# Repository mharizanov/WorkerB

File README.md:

WorkerB
=======

This is my latest project, the “Worker Bee”. It is an ATMega32U4-based Arduino compatible board running at 8Mhz, 
specially designed for low-power battery operation. There is a slot on the board to fit a 2.4Ghz nRF24L01 breakout 
module (not included, optional); Power to that slot is controlled via a MOSFET, so that the MCU is in control and 
can power the nRF24L01 whenever/if necessary and save power.

The board can be powered via a single AAA battery using an optional LTC3525 boost regulator, a CR2032 battery or 
any other 2.6-5.5V source (via the on-board MCP1700 for voltages >3.3V or directly at the VCC in)

http://harizanov.com/product/workerb/

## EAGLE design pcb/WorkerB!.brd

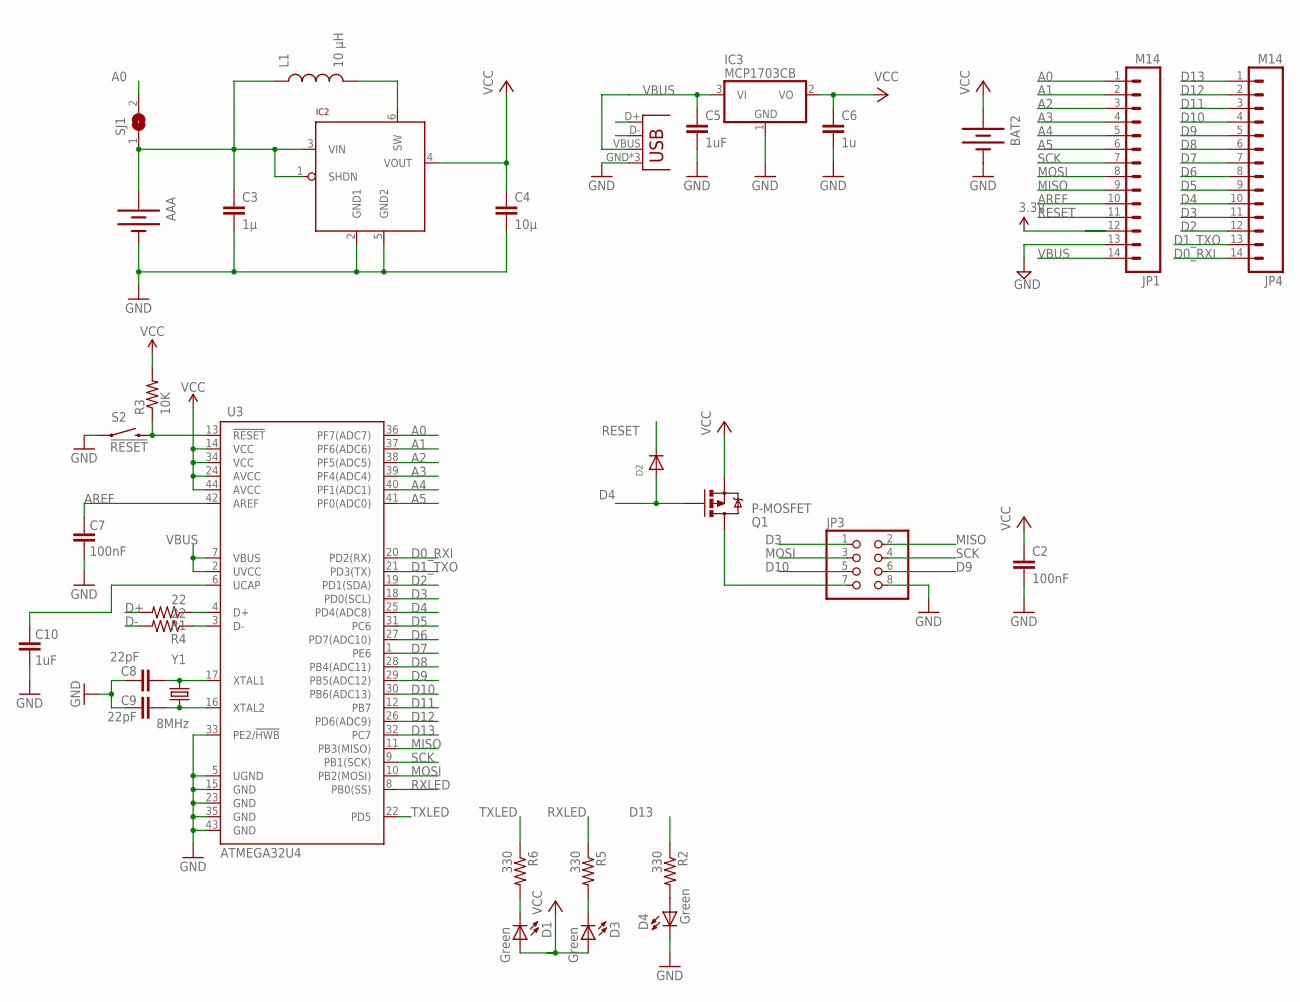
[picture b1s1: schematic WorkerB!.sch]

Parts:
AAA: BATTERYAAA-JL; BATTERY-AAA-JL
BAT2: BATTERY20PTH; BATTCOM_20MM_PTH
C2: 100nF; C0603K
C3: 1µ; 0603-CAP
C4: 10µ; 0805
C5: 1uF; C0603K
C6: 1u; C0603K
C7: 100nF; 0402-CAP
C8, C9: 22pF; 0402-CAP
C10: 1uF; 0402-CAP
D1, D3, D4: Green; LED-0603
D2: DIODESOD-323F; SOD-323F
IC2: LTC3525; SC70
IC3: MCP1703CB; SOT23
JP1, JP4: M14; 1X14
JP2: USB-MICROB
JP3: PINHD-2X4; 2X04
L1: 10 µH; 1210
Q1: P-MOSFET; SOT23
R1, R4: 22; 0402-RES
R2, R5, R6: 330; 0402-RES
R3: 10K; 0402-RES
S2: !RESET; TACTILE_SWITCH_SMD
SJ1: SJ
U3: ATMEGA32U4; QFN-44-NOPAD
Y1: 8MHz; CRYSTAL-SMD-5X3

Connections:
A0: JP1.1, SJ1.2, U3.36 (PF7(ADC7))
A1: JP1.2, U3.37 (PF6(ADC6))
A2: JP1.3, U3.38 (PF5(ADC5))
A3: JP1.4, U3.39 (PF4(ADC4))
A4: JP1.5, U3.40 (PF1(ADC1))
A5: JP1.6, U3.41 (PF0(ADC0))
AREF: C7.2, JP1.10, U3.42 (AREF)
D0_RXI: JP4.14, U3.20 (PD2(RX))
D1_TXO: JP4.13, U3.21 (PD3(TX))
D2: JP4.12, U3.19 (PD1(SDA))
D3: JP3.1, JP4.11, U3.18 (PD0(SCL))
D4: D2.A, JP4.10, Q1.1 (G), U3.25 (PD4(ADC8))
D5: JP4.9, U3.31 (PC6)
D6: JP4.8, U3.27 (PD7(ADC10))
D7: JP4.7, U3.1 (PE6)
D8: JP4.6, U3.28 (PB4(ADC11))
D9: JP3.6, JP4.5, U3.29 (PB5(ADC12))
D10: JP3.5, JP4.4, U3.30 (PB6(ADC13))
D11: JP4.3, U3.12 (PB7)
D12: JP4.2, U3.26 (PD6(ADC9))
D13: JP4.1, R2.1, U3.32 (PC7)
D+: JP2.D+, R1.2
D-: JP2.D-, R4.2
GND: AAA.GND@1 (-), BAT2.2 (-), C2.2, C3.2, C4.2, C5.2, C6.2, C7.1, C8.2, C9.2, C10.1, D4.C, IC2.2 (GND1), IC2.5 (GND2), IC3.1 (GND), JP1.13, JP2.GND, JP2.MT1 (GND), JP2.MT2 (GND), JP3.8, S2.1, U3.5 (UGND), U3.15 (GND), U3.23 (GND), U3.33 (PE2/!HWB), U3.35 (GND), U3.43 (GND)
MISO: JP1.9, JP3.2, U3.11 (PB3(MISO))
MOSI: JP1.8, JP3.3, U3.10 (PB2(MOSI))
unnamed: C9.1, U3.16 (XTAL2), Y1.1
unnamed: R1.1, U3.4 (D+)
unnamed: D4.A, R2.2
unnamed: C8.1, U3.17 (XTAL1), Y1.3 (2)
unnamed: C10.2, U3.6 (UCAP)
unnamed: D3.C, R5.2
unnamed: R4.1, U3.3 (D-)
unnamed: D1.C, R6.2
unnamed: JP3.7, Q1.3 (D)
unnamed: IC2.6 (SW), L1.2
RESET: D2.C, JP1.11, R3.1, S2.3 (2), U3.13 (!RESET)
RXLED: R5.1, U3.8 (PB0(SS))
SCK: JP1.7, JP3.4, U3.9 (PB1(SCK))
TXLED: R6.1, U3.22 (PD5)
VBUS: C5.1, IC3.3 (VI), JP1.14, JP2.VBUS, U3.2 (UVCC), U3.7 (VBUS)
VCC: BAT2.1 (+), C2.1, C4.1, C6.1, D1.A, D3.A, IC2.4 (VOUT), IC3.2 (VO), JP1.12, Q1.2 (S), R3.2, U3.14 (VCC), U3.24 (AVCC), U3.34 (VCC), U3.44 (AVCC)
VIN: AAA.PWR@1 (+), C3.1, IC2.1 (SHDN), IC2.3 (VIN), L1.1, SJ1.1

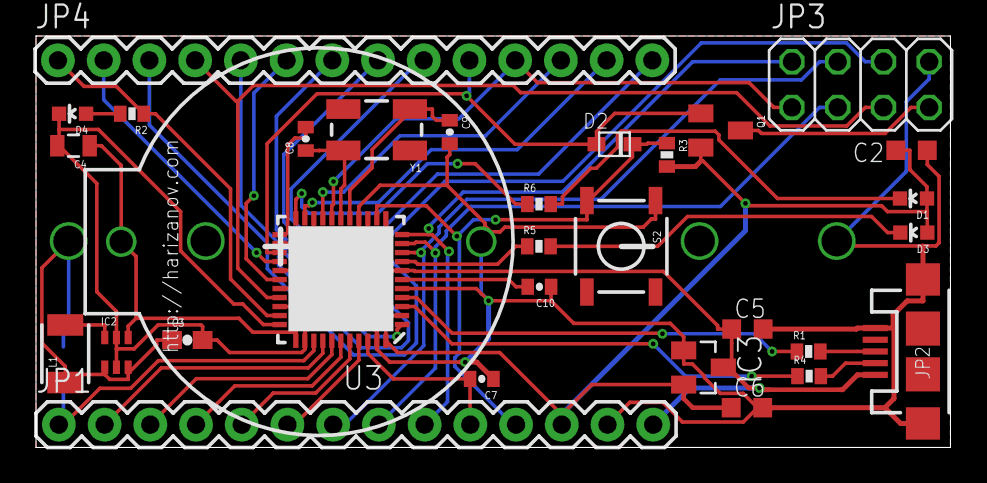
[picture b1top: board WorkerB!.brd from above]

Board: 2 copper layers, 50.8 x 22.9 mm, 33 parts (1 on the bottom side), 43 nets.

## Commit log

2013-06-20 initial
2013-06-21 basic examples with nRF24L01

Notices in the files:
parts and their libraries:
SparkFun: Licensing: CC v3.0 Share-Alike You are welcome to use this library for commercial purposes.
